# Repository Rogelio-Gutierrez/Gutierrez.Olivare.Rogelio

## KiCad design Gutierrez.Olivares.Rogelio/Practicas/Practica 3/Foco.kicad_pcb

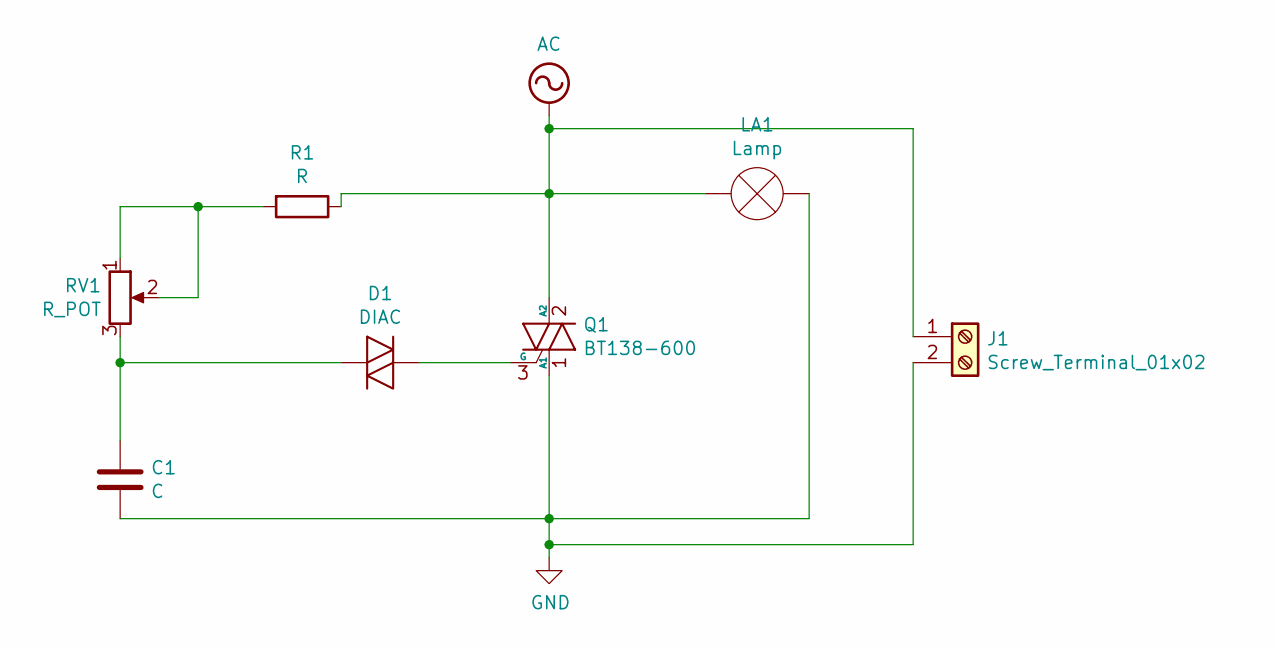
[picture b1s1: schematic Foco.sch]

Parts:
C1: C; C_Axial_L22.0mm_D9.5mm_P27.50mm_Horizontal
D1: DIAC; D_DO-34_SOD68_P7.62mm_Horizontal
J1: Screw_Terminal_01x02; SolderWirePad_1x02_P3.81mm_Drill1.2mm
LA1: Lamp; SolderWirePad_1x02_P3.81mm_Drill1.2mm
Q1: BT138-600; TO-220-3_Vertical
R1: R; R_Axial_DIN0204_L3.6mm_D1.6mm_P7.62mm_Horizontal
RV1: R_POT; Potentiometer_Alps_RK097_Single_Horizontal

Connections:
AC: J1.1, LA1.1 (-), Q1.2 (A2), R1.1
GND: C1.2, J1.2, LA1.2 (+), Q1.1 (A1)
unnamed: C1.1, D1.1 (K), RV1.3
unnamed: D1.2 (A), Q1.3 (G)
unnamed: R1.2, RV1.1, RV1.2

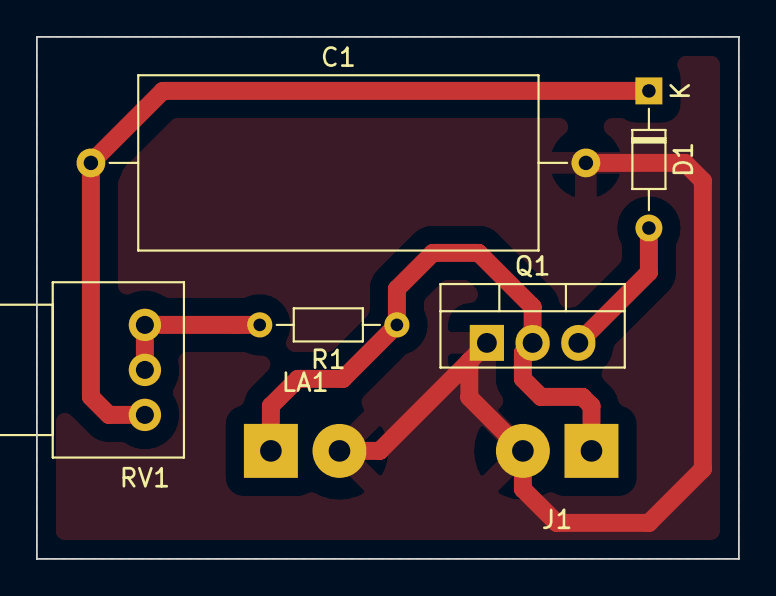
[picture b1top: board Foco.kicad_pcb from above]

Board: 2 copper layers, 39.0 x 29.0 mm, 7 parts (0 on the bottom side), 5 nets.

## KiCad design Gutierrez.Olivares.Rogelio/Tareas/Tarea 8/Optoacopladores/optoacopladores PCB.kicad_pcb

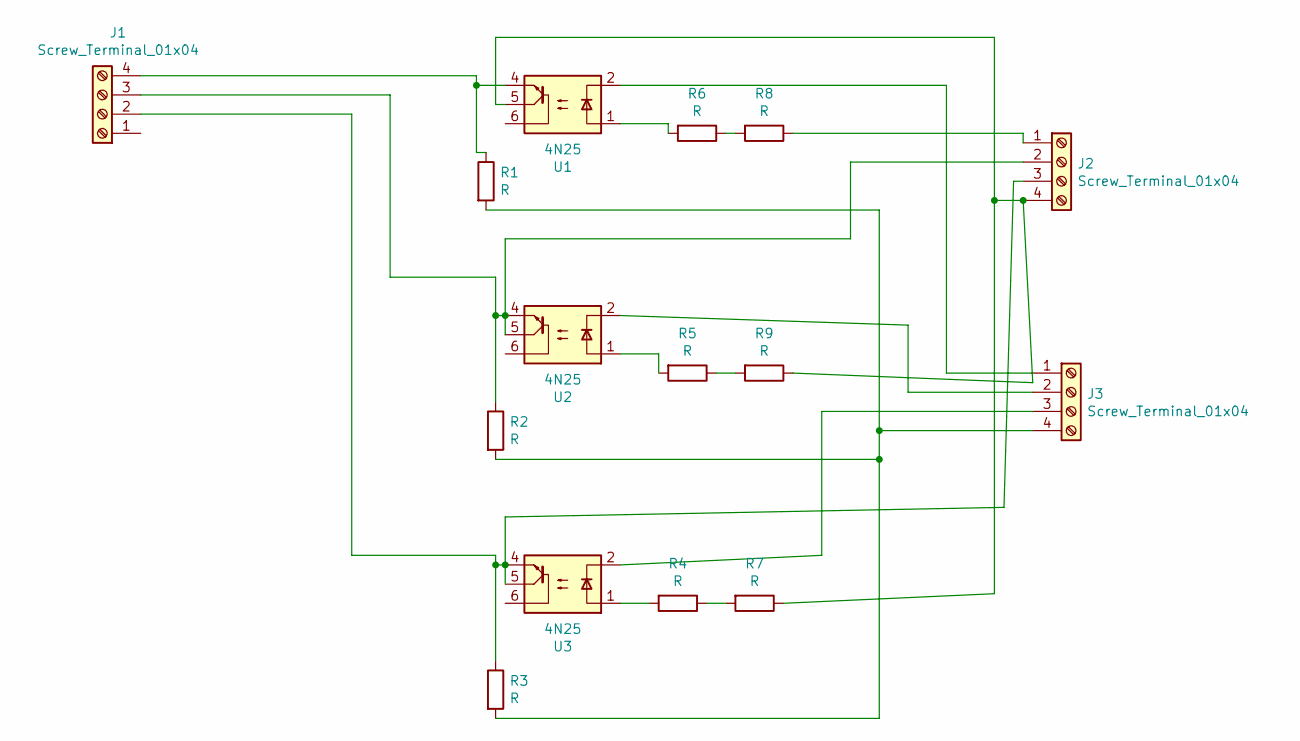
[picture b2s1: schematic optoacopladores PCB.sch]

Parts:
J1, J2, J3: Screw_Terminal_01x04; TerminalBlock_Wuerth_691311400102_P7.62mm
R1: R; R_Axial_DIN0207_L6.3mm_D2.5mm_P10.16mm_Horizontal
R2, R3, R4, R5, R6, R7, R8, R9: R; R_Axial_DIN0204_L3.6mm_D1.6mm_P5.08mm_Vertical
U1, U2, U3: 4N25; DIP-6_W7.62mm

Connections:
unnamed: J1.2, J2.3, R3.1, U3.4, U3.5
unnamed: J1.3, J2.2, R2.1, U2.4, U2.5
unnamed: J1.4, R1.1, U1.4
unnamed: J2.1, R8.1
unnamed: J2.4, R7.1, R9.1, U1.5
unnamed: J3.1, U1.2
unnamed: J3.2, U2.2
unnamed: J3.3, U3.2
unnamed: J3.4, R1.2, R2.2, R3.2
unnamed: R4.1, R7.2
unnamed: R4.2, U3.1
unnamed: R5.1, R9.2
unnamed: R5.2, U2.1
unnamed: R6.1, R8.2
unnamed: R6.2, U1.1

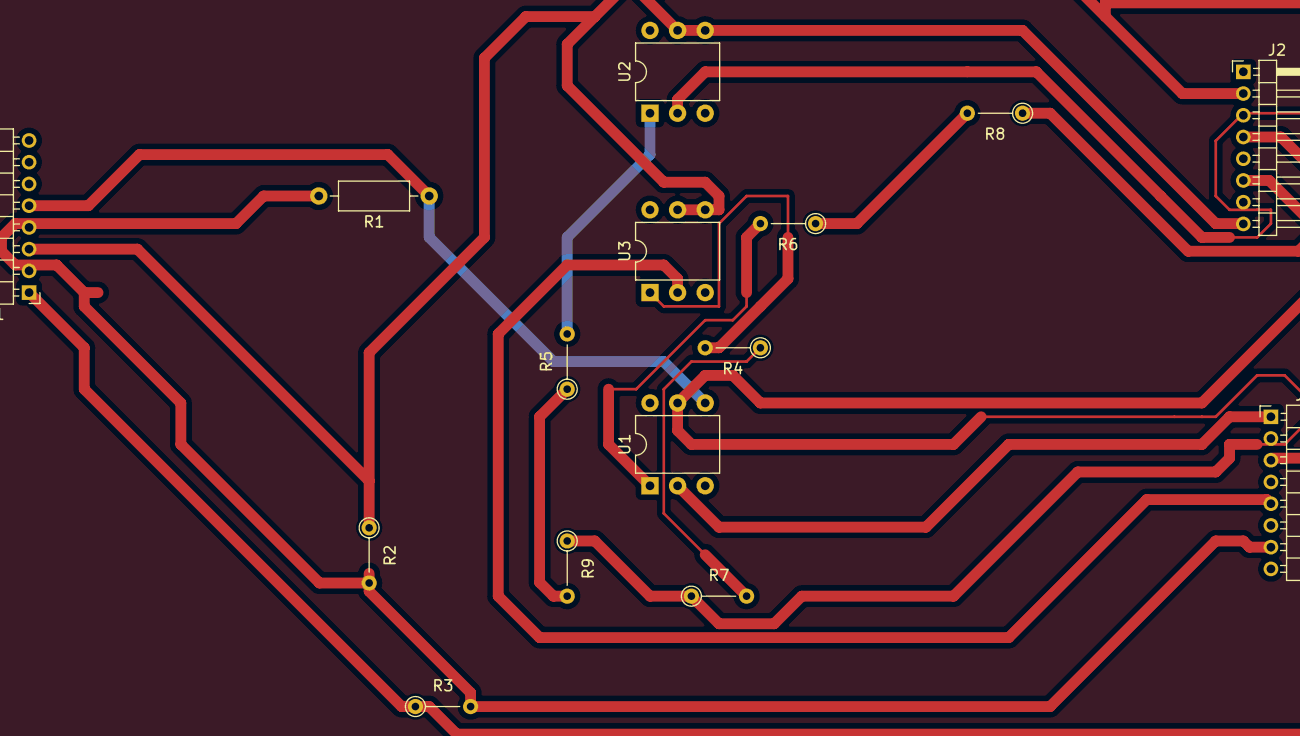
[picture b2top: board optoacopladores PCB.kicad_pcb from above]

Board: 2 copper layers, 15 parts (0 on the bottom side), 15 nets.

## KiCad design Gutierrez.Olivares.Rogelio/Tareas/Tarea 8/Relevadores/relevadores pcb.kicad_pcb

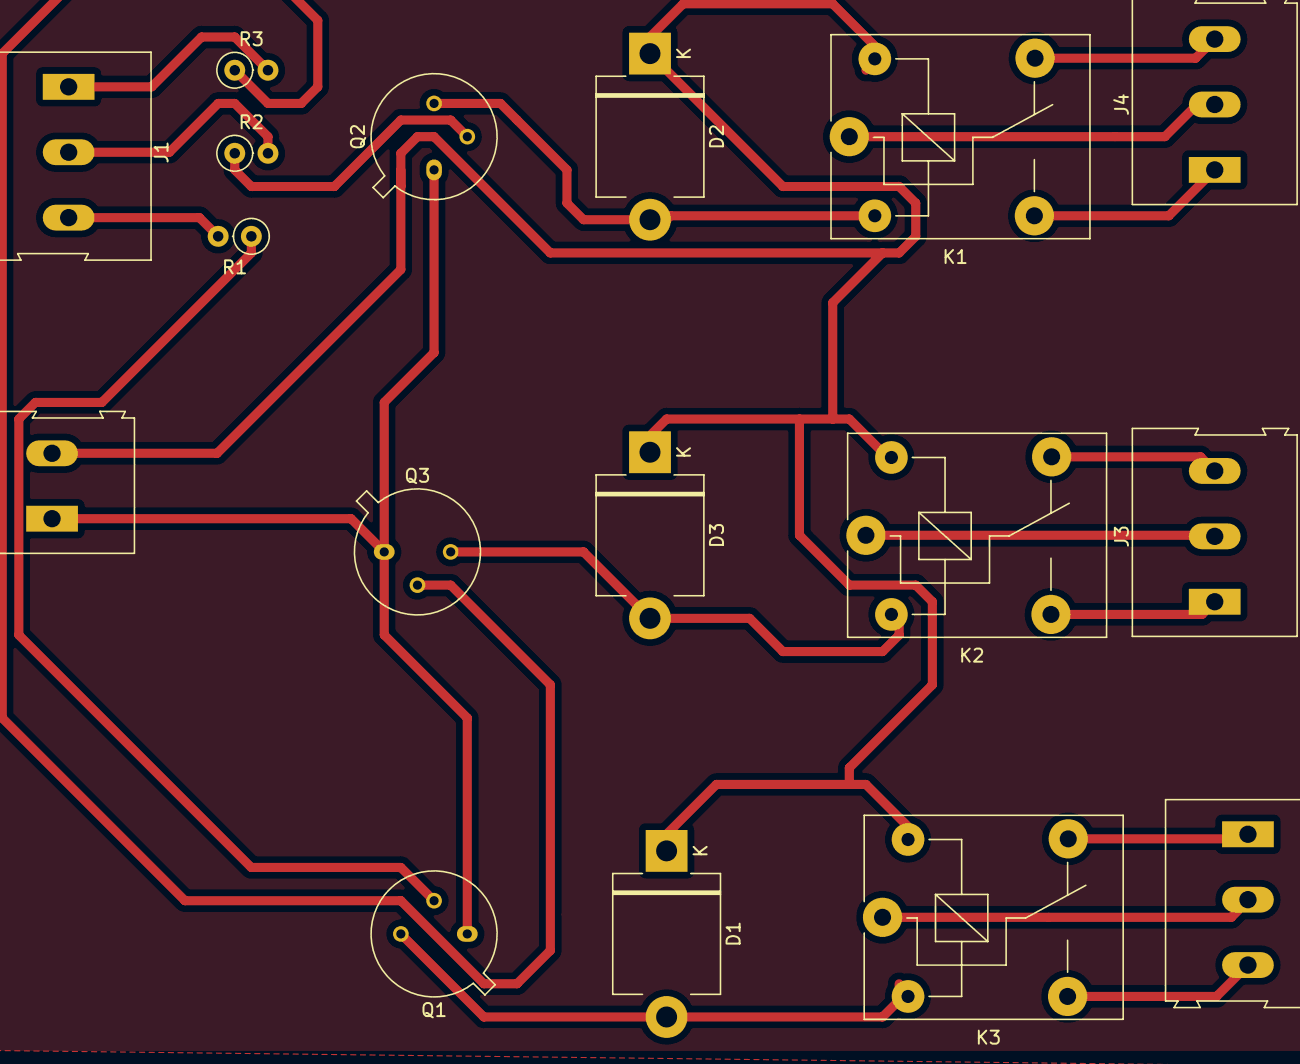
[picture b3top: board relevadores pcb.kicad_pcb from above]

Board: 2 copper layers, 17 parts (0 on the bottom side), 14 nets.

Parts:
D1, D2, D3: D; D_5KPW_P12.70mm_Horizontal
J1, J3, J4, J5: Screw_Terminal_01x03; TerminalBlock_Altech_AK300-3_P5.00mm
J2: Screw_Terminal_01x02; TerminalBlock_Altech_AK300-2_P5.00mm
K1, K2, K3: HF3-03; Relay_SPDT_SANYOU_SRD_Series_Form_C
Q1, Q2, Q3: 2N2219; TO-39-3
R1, R2, R3: R; R_Axial_DIN0207_L6.3mm_D2.5mm_P2.54mm_Vertical

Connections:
unnamed: D1.1, D2.1, D3.1, J2.2, K1.1, K2.1, K3.1
unnamed: D1.2, Q1.3
unnamed: D2.2, Q2.3
unnamed: D3.2, Q3.3
unnamed: J1.1, R3.2
unnamed: J1.2, R2.2
unnamed: J1.3, R1.2
unnamed: J2.1, Q1.1, Q2.1, Q3.1
unnamed: J3.3, K2.2, K2.5
unnamed: J4.3, K1.2, K1.5
unnamed: J5.3, K3.2, K3.5
unnamed: Q1.2, R1.1
unnamed: Q2.2, R2.1
unnamed: Q3.2, R3.1

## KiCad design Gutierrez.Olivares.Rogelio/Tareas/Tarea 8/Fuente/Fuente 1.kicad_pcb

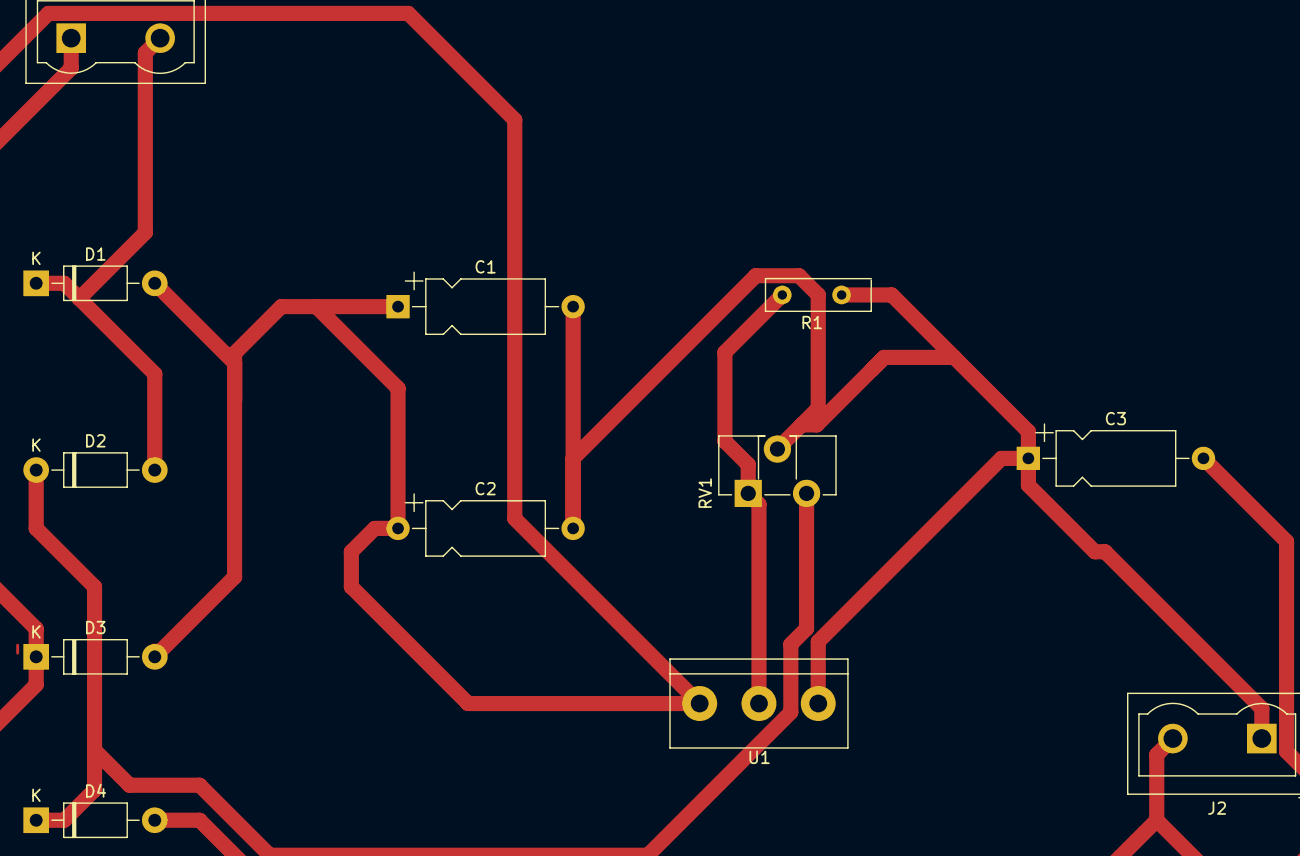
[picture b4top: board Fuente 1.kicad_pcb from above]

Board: 2 copper layers, 12 parts (0 on the bottom side), 5 nets.

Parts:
C1: 2200uF; CP_Axial_L10.0mm_D4.5mm_P15.00mm_Horizontal
C2: 0.1uF; CP_Axial_L10.0mm_D4.5mm_P15.00mm_Horizontal
C3: 270uF; CP_Axial_L10.0mm_D4.5mm_P15.00mm_Horizontal
D1, D2, D3, D4: 1N4007; D_DO-41_SOD81_P10.16mm_Horizontal
J1, J2: Screw_Terminal_01x02; TerminalBlock_Wuerth_691311400102_P7.62mm
R1: 10K; R_Array_SIP4
RV1: 5K; Potentiometer_ACP_CA9-H3,8_Horizontal
U1: LM317_TO3; TerminalBlock_bornier-3_P5.08mm

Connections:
unnamed: R1.4, RV1.1, U1.2
unnamed: C1.2, C2.2, C3.1, J2.1, R1.2, RV1.2, U1.1
unnamed: D1.1, D2.2, D3.1, D4.2, J1.1, J1.2
unnamed: C1.1, C2.1, C3.2, D1.2, D3.2, J2.2, U1.3
unnamed: D2.1, D4.1, RV1.3
